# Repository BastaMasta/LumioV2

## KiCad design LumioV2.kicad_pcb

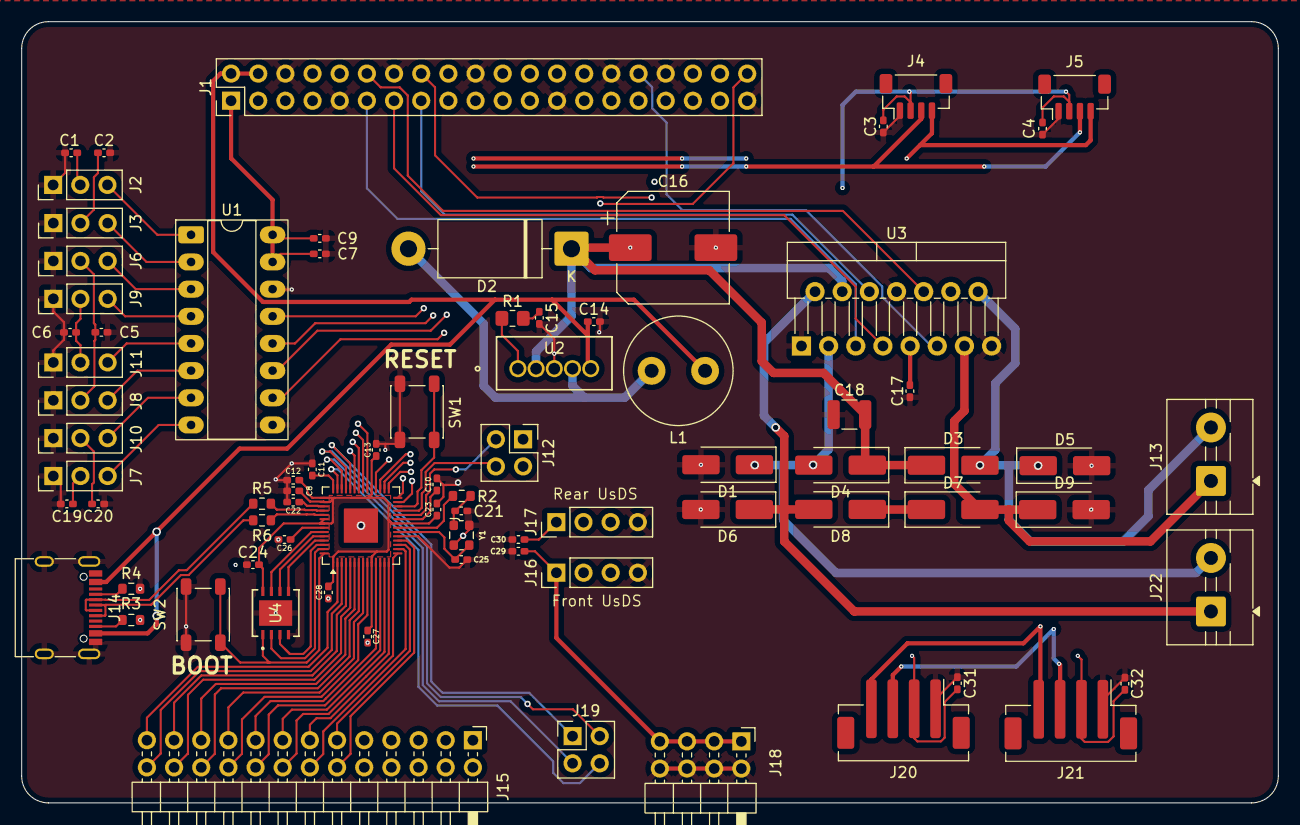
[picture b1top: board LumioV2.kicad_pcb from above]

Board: 4 copper layers, 117.5 x 73.0 mm, 79 parts (1 on the bottom side), 86 nets.

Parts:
C1, C2, C3, C4, C5, C6, C7, C8, C9, C11, C12, C14, C17, C19, C20, C24, C28, C29, C30, C31, C32: 100nF; C_0402_1005Metric_Pad0.74x0.62mm_HandSolder
C10, C13, C22, C23, C26, C27: 1uF; C_0402_1005Metric_Pad0.74x0.62mm_HandSolder
C15: 0.33uF; C_0402_1005Metric_Pad0.74x0.62mm_HandSolder
C16, C33: 680uF; CP_Elec_10x10
C18: 100nF; C_1210_3225Metric
C21, C25: 15pF; C_0402_1005Metric_Pad0.74x0.62mm_HandSolder
D1, D3, D4, D5, D6, D7, D8, D9: SS34B; D_SMA_Handsoldering
D2: 1N5821; D_DO-201AD_P15.24mm_Horizontal
J1: Raspi 5; PinHeader_2x20_P2.54mm_Vertical
J2, J3, J6, J7, J8, J9, J10, J11: Analog Input; PinHeader_1x03_P2.54mm_Vertical
J4: I2C POINT 1 - QWIIC; JST_SH_BM04B-SRSS-TB_1x04-1MP_P1.00mm_Vertical
J5: I2C POINT 2 - QWIIC; JST_SH_BM04B-SRSS-TB_1x04-1MP_P1.00mm_Vertical
J12: Header programmer; PinHeader_2x02_P2.54mm_Vertical
J13: MOTOR B; TerminalBlock_MaiXu_MX126-5.0-02P_1x02_P5.00mm
J14: USB_C_Receptacle_USB2.0_14P; USB_C_Receptacle_G-Switch_GT-USB-7010ASV
J15: Conn_02x13_Odd_Even; PinHeader_2x13_P2.54mm_Horizontal
J16: US Dist - Front; PinHeader_1x04_P2.54mm_Vertical
J17: US Dist - Back; PinHeader_1x04_P2.54mm_Vertical
J18: Sensor power lines; PinHeader_2x04_P2.54mm_Horizontal
J19: Conn_02x02_Odd_Even; PinHeader_2x02_P2.54mm_Vertical
J20: I2C POINT 4 - JST-PH; JST_PH_B4B-PH-SM4-TB_1x04-1MP_P2.00mm_Vertical
J21: I2C POINT 3 - JST-PH; JST_PH_B4B-PH-SM4-TB_1x04-1MP_P2.00mm_Vertical
J22: MOTOR A; TerminalBlock_MaiXu_MX126-5.0-02P_1x02_P5.00mm
L1: 100uH; L_Radial_D10.0mm_P5.00mm_Fastron_07M
R1: 2.2K; R_0805_2012Metric_Pad1.20x1.40mm_HandSolder
R2: 1K; R_0603_1608Metric
R3, R4: 5.1K; R_0603_1608Metric
R5, R6: 27; R_0603_1608Metric
SW1, SW2: SW_Push; SW_SPST_PTS647_Sx50
U1: MCP3008; DIP-16_W7.62mm_Socket_LongPads
U2: LM2577T-ADJ/NOPB; T05A_TEX
U3: L298N; TO-220-15_P2.54x5.08mm_StaggerOdd_Lead4.58mm_Vertical
U4: DFN_XGIQ_TR_WIN; DFN_XGIQ TR_WIN-M
U5: RP2040; QFN-56-1EP_7x7mm_P0.4mm_EP3.2x3.2mm
Y1: ECS-2520MV-xxx-xx; Oscillator_SMD_ECS_2520MV-xxx-xx-4Pin_2.5x2.0mm

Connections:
+1V1: C10.2, C22.2, C26.2, U5.23 (DVDD), U5.45 (VREG_VOUT), U5.50 (DVDD)
+3V3: C1.1, C2.1, C3.2, C4.2, C5.1, C6.1, C7.1, C8.2, C9.1, C11.2, C12.2, C13.2, C19.1, C20.1, C23.2, C24.2, C27.2, C28.2, C29.2, C30.2, C31.2, C32.2, J1.1, J1.17 (3V3), J2.2, J3.2, J4.2, J5.2, J6.2, J7.2, J8.2, J9.2, J10.2, J11.2, J16.1, J17.1, J18.1, J18.3, J18.5, J18.7, J20.2, J21.2, U1.15 (Vref), U1.16 (Vdd), U4.8, U5.1 (IOVDD), U5.10 (IOVDD), U5.22 (IOVDD), U5.33 (IOVDD), U5.42 (IOVDD), U5.43 (ADC_AVDD), U5.44 (VREG_VIN), U5.48 (USB_VDD), U5.49 (IOVDD)
+5V: C14.1, C17.2, J1.2 (5V), J1.4 (5V), J14.A4 (VBUS), J14.A9 (VBUS), J14.B4 (VBUS), J14.B9 (VBUS), L1.1, U2.5 (VIN), U3.9 (Vss)
/SCL: J1.5, J4.4, J5.4, J20.4, J21.4
/SDA: J1.3 (SDA1), J4.3, J5.3, J20.3, J21.3
/USB_N: J14.A7 (D-), J14.B7 (D-), R5.1
/USB_P: J14.A6 (D+), J14.B6 (D+), R6.2
GND: C1.2, C2.2, C3.1, C4.1, C5.2, C6.2, C7.2, C8.1, C9.2, C10.1, C11.1, C12.1, C13.1, C14.2, C15.1, C16.2, C17.1, C18.1, C19.2, C20.2, C21.1, C22.1, C23.1, C24.1, C25.2, C26.1, C27.1, C28.1, C29.1, C30.1, C31.1, C32.1, C33.2, D1.2 (A), D5.2 (A), D6.2 (A), D9.2 (A), J1.6 (GND), J1.9 (GND), J1.14 (GND), J1.20 (GND), J1.25 (GND), J1.30 (GND), J1.34 (GND), J1.39 (GND), J2.1, J3.1, J4.1, J5.1, J6.1, J7.1, J8.1, J9.1, J10.1, J11.1, J14.A1 (GND), J14.A12 (GND), J14.B1 (GND), J14.B12 (GND), J14.S1 (SHIELD), J16.4, J17.4, J18.2, J18.4, J18.6, J18.8, J20.1, J21.1, R3.1, R4.2, SW1.1, SW2.1, U1.9 (DGND), U1.14 (AGND), U2.3 (GND), U3.1 (SENSE_A), U3.8 (GND), U3.15 (SENSE_B), U4.4, U4.9, U5.19 (TESTEN), U5.57 (GND), Y1.2 (GND), Y1.4 (VDD)
unnamed: C15.2, R1.1
unnamed: D1.1 (K), D4.2 (A), J22.2, U3.3 (OUT2)
unnamed: D2.2 (A), L1.2, U2.4 (SW)
unnamed: C16.1, C18.2, C33.1, D2.1 (K), D3.1 (K), D4.1 (K), D7.1 (K), D8.1 (K), U2.2 (FB), U3.4 (Vs)
unnamed: D3.2 (A), D5.1 (K), J13.2, U3.14 (OUT4)
unnamed: D6.1 (K), D8.2 (A), J22.1, U3.2 (OUT1)
unnamed: D7.2 (A), D9.1 (K), J13.1, U3.13 (OUT3)
unnamed: J1.8, J15.26, U5.3 (GPIO1)
unnamed: J1.10, J15.25, U5.2 (GPIO0)
unnamed: J1.11, U3.5 (IN1)
unnamed: J1.12, U3.10 (IN3)
unnamed: J1.13, U3.7 (IN2)
unnamed: J1.15, U3.6 (EnA)
unnamed: J1.16, U3.12 (IN4)
unnamed: J1.18, J12.1
unnamed: J1.22, J12.2
unnamed: J1.29, J16.2
unnamed: J1.31, J16.3
unnamed: J1.32, U3.11 (EnB)
unnamed: J1.33, J17.2
unnamed: J1.35, U1.12 (Dout)
unnamed: J1.36, U1.10 (~CS/SHDN)
unnamed: J1.37, J17.3
unnamed: J1.38, U1.11 (Din)
unnamed: J1.40, U1.13 (CLK)
unnamed: J14.A5 (CC1), R4.1
unnamed: J14.B5 (CC2), R3.2
unnamed: J15.1, U5.36 (GPIO24)
unnamed: J15.2, U5.37 (GPIO25)
unnamed: J15.3, U5.34 (GPIO22)
unnamed: J15.4, U5.35 (GPIO23)
unnamed: J15.5, U5.31 (GPIO20)
unnamed: J15.6, U5.32 (GPIO21)
unnamed: J15.7, U5.29 (GPIO18)
unnamed: J15.8, U5.30 (GPIO19)
unnamed: J15.9, U5.27 (GPIO16)
unnamed: J15.10, U5.28 (GPIO17)
unnamed: J15.11, U5.17 (GPIO14)
unnamed: J15.12, U5.18 (GPIO15)
unnamed: J15.13, U5.15 (GPIO12)
unnamed: J15.14, U5.16 (GPIO13)
unnamed: J15.15, U5.13 (GPIO10)
unnamed: J15.16, U5.14 (GPIO11)
unnamed: J15.17, U5.11 (GPIO8)
unnamed: J15.18, U5.12 (GPIO9)
unnamed: J15.19, U5.8 (GPIO6)
unnamed: J15.20, U5.9 (GPIO7)
unnamed: J15.21, U5.6 (GPIO4)
unnamed: J15.22, U5.7 (GPIO5)
unnamed: J15.23, U5.4 (GPIO2)
unnamed: J15.24, U5.5 (GPIO3)
unnamed: J2.3, U1.1 (CH0)
unnamed: J11.3, U1.5 (CH4)
unnamed: J3.3, U1.2 (CH1)
unnamed: J9.3, U1.4 (CH3)
unnamed: J10.3, U1.7 (CH6)
unnamed: J8.3, U1.6 (CH5)
unnamed: J6.3, U1.3 (CH2)
unnamed: J7.3, U1.8 (CH7)
unnamed: J12.3, U5.24 (SWCLK)
unnamed: J12.4, U5.25 (SWDIO)
unnamed: J19.1, U5.38 (GPIO26/ADC0)
unnamed: J19.2, U5.39 (GPIO27/ADC1)
unnamed: J19.3, U5.40 (GPIO28/ADC2)
unnamed: J19.4, U5.41 (GPIO29/ADC3)
unnamed: R1.2, U2.1 (COMP)
unnamed: U4.6, U5.52 (QSPI_SCLK)
unnamed: U4.5, U5.53 (QSPI_SD0)
unnamed: U4.2, U5.55 (QSPI_SD1)
unnamed: SW2.2, U4.1, U5.56 (~QSPI_SS)
unnamed: U4.7, U5.51 (QSPI_SD3)
unnamed: U4.3, U5.54 (QSPI_SD2)
unnamed: SW1.2, U5.26 (RUN)
unnamed: R5.2, U5.46 (USB_DM)
unnamed: R6.1, U5.47 (USB_DP)
unnamed: C25.1, U5.20 (XIN), Y1.3 (OUT)
unnamed: R2.1, U5.21 (XOUT)
unnamed: C21.2, R2.2, Y1.1 (Tri-State)

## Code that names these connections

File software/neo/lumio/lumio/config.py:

"""
lumio/config.py
---------------
Hardware pin definitions for Lumio V2 (BCM GPIO numbering).
All values match the V2 schematic and user-confirmed wiring.
"""

# ── Motor driver (L298N) ──────────────────────────────────────────────────────
# Motor A  =  Left  wheel
MOTOR_A_IN1  = 17   # Forward
MOTOR_A_IN2  = 27   # Backward
MOTOR_A_ENA  = 22   # PWM speed (Hardware PWM capable on Pi 5)

# Motor B  =  Right wheel
MOTOR_B_IN3  = 18   # Forward
MOTOR_B_IN4  = 23   # Backward
MOTOR_B_ENB  = 12   # PWM speed (Hardware PWM capable on Pi 5)

# ── Ultrasonic distance sensors (direct RPi5 GPIO for low latency) ────────────
FRONT_TRIG   = 5
FRONT_ECHO   = 6
BACK_TRIG    = 13
BACK_ECHO    = 26   # Changed from old REAR_ECHO=19 per V2 schematic

# ── MCP3008 ADC (SPI1 — software-mapped pins) ────────────────────────────────
ADC_CS       = 16   # SPI1 CE2
ADC_MOSI     = 20   # SPI1 MOSI
ADC_MISO     = 35   # SPI1 MISO  (BCM 35 = physical pin 19 on Pi 5 40-pin header)
ADC_CLK      = 21   # SPI1 CLK

# ── RP2040 co-processor UART ──────────────────────────────────────────────────
# rp2040 GPIO1 → RPi5 GPIO15 (RXD)
# rp2040 GPIO2 → RPi5 GPIO14 (TXD)
RP2040_UART_PORT = "/dev/ttyAMA0"   # UART0 on Pi 5 (GPIO14/15)
RP2040_UART_BAUD = 115200

# ── I2C bus ───────────────────────────────────────────────────────────────────
I2C_SCL      = 3    # I2C1 SCL
I2C_SDA      = 2    # I2C1 SDA
I2C_BUS      = 1    # /dev/i2c-1

# ── Motion parameters ─────────────────────────────────────────────────────────
LINEAR_SPEED_MPS     = 0.7    # metres per second at 50 % duty
ROTATION_SPEED_DPS   = 270    # degrees per second at 50 % duty
OBSTACLE_THRESHOLD_CM = 20    # emergency-stop distance (cm)
PWM_FREQUENCY_HZ     = 200    # motor PWM frequency

# ── Hotspot / WiFi provisioning ───────────────────────────────────────────────
HOTSPOT_SSID     = "Lumio-Setup"
HOTSPOT_PASSWORD = "lumio1234"
HOTSPOT_IP       = "192.168.50.1"
PROVISION_PORT   = 8080

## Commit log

2026-03-28 init commit
2026-03-28 Added safety and pull circuit to the L298N block outputs
2026-03-30 correcrted pin orde rin schematics and added most footprints
2026-04-05 re-started routing, for clearer routes. also moved to dsi conenctor for display
2026-04-06 finished routing, added 3d files for most parts
2026-04-06 added project report, insternship report and diary
2026-04-07 added code files
2026-04-07 relocated files
2026-04-09 Create CNAME
2026-04-09 removed tooling guide
2026-04-09 added bom link
2026-04-09 updated structure diagram
